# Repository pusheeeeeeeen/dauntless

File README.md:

# LiHv battery charger V1+V2
LiHv battery charger capable of charging LiHv batteries up to 4.35v, custom 3d designed case for 3d printing and an on-off switch. V1 is the simplest module, just to be available for cheaper and easier production of 4.35v LiHv chargers. V2 is equipped with a buzzer, OLED display, and XIAO RP2040 module to track battery percentage, and to alert the user when the battery is done charging. 

## V1: Mr. Barebones
### 3D rendering

### Schematic

### PCB Layout

## V2: The Upgrade
### 3D rendering

### Schematic

### PCB Layout

## BOM:
https://docs.google.com/spreadsheets/d/1y4eYakeZhQ_Du6QSC2gYvQQuMS255J4ouP4txh3QHf0/edit?gid=0#gid=0

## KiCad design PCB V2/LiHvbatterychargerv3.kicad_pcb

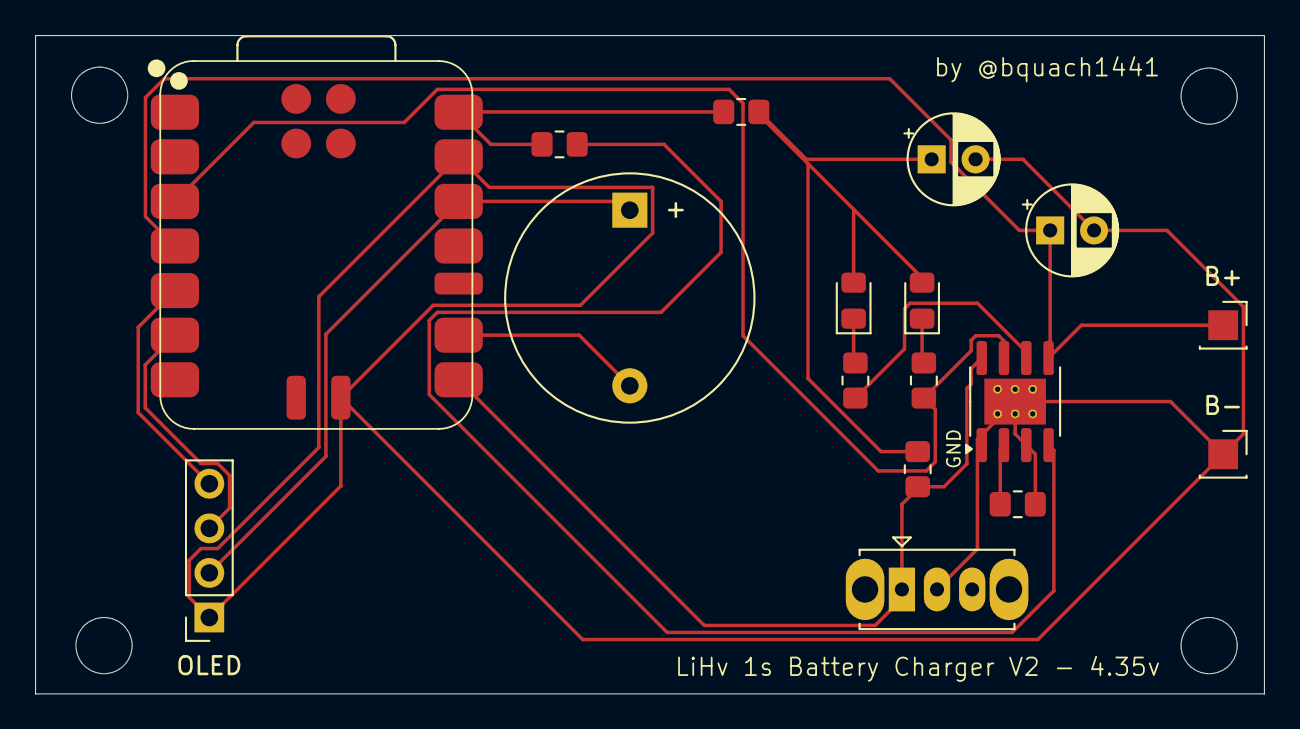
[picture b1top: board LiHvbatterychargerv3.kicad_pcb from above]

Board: 2 copper layers, 70.0 x 37.5 mm, 17 parts (0 on the bottom side), 15 nets.

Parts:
B+: Conn_01x01; PinSocket_1x01_P2.54mm_Vertical
B-: Conn_01x01; PinSocket_1x01_P2.54mm_Vertical
BZ1: Buzzer; Buzzer_D14mm_H7mm_P10mm
C2, C3: 10uF; CP_Radial_D5.0mm_P2.50mm
D1, D2: LED; LED_0805_2012Metric_Pad1.15x1.40mm_HandSolder
OLED: "OLED Display"; PinSocket_1x04_P2.54mm_Vertical
R3: 2.2k; R_0805_2012Metric_Pad1.20x1.40mm_HandSolder
R4, R5: 1k; R_0805_2012Metric_Pad1.20x1.40mm_HandSolder
R6, R8: 0.2; R_0805_2012Metric_Pad1.20x1.40mm_HandSolder
R7: 10k; R_0805_2012Metric_Pad1.20x1.40mm_HandSolder
SW1: SW_SPST; SW_Slide_SPDT_Straight_CK_OS102011MS2Q
U1: TP4056X-42-ESOP8; SOIC-8-1EP_3.9x4.9mm_P1.27mm_EP2.62x3.51mm_ThermalVias
U2: XIAO-RP2040-SMD

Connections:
GND: B-.1, C2.2, C3.2, OLED.1, R3.1, SW1.2 (B), U1.1 (TEMP), U1.3 (GND), U1.9 (EPAD), U2.13 (GND), U2.33 (GND)
unnamed: BZ1.1 (+), OLED.2, U2.12 (3V3)
unnamed: BZ1.2 (-), U2.9 (P2_D8_SCK)
unnamed: C2.1, D1.2 (A), D2.2 (A), R6.1, R7.2
unnamed: D1.1 (K), R5.2
unnamed: D2.1 (K), R4.2
unnamed: OLED.3, U2.6 (P7_SCL_D5)
unnamed: OLED.4, U2.5 (P6_SDA_D4)
unnamed: B+.1, C3.1, U1.5 (BAT), U2.4 (P29_A3_D3)
unnamed: R7.1, SW1.1 (A), U1.8 (CE), U2.8 (P1_D7_RX)
unnamed: R3.2, U1.2 (PROG)
unnamed: R8.1, U1.4 (V_{CC})
unnamed: R5.1, U1.7 (~CHRG), U2.3 (P28_A2_D2)
unnamed: R4.1, U1.6 (~STDBY)
unnamed: R6.2, R8.2, U2.14 (VBUS)

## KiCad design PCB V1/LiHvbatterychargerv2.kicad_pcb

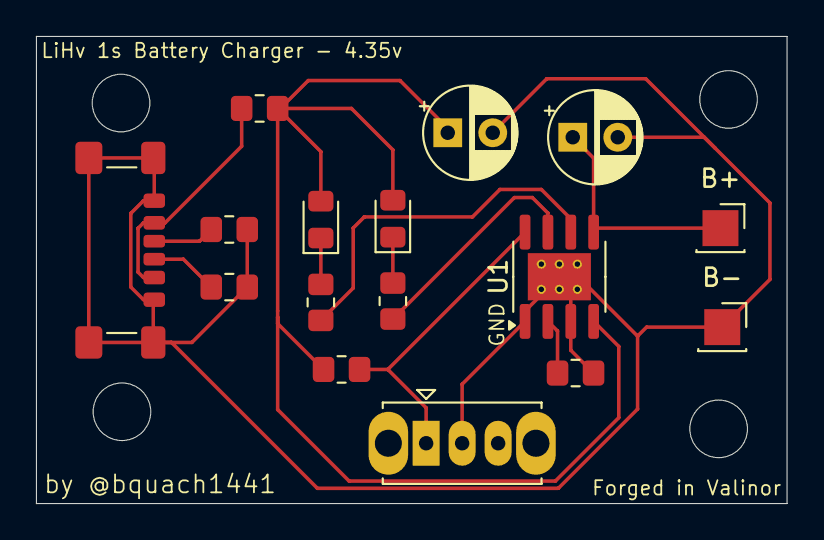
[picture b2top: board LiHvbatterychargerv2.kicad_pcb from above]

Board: 2 copper layers, 41.7 x 25.9 mm, 16 parts (0 on the bottom side), 12 nets.

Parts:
B+: Conn_01x01; PinSocket_1x01_P2.54mm_Vertical
B-: Conn_01x01; PinSocket_1x01_P2.54mm_Vertical
C2, C3: 10uF; CP_Radial_D5.0mm_P2.50mm
D1, D2: LED; LED_0805_2012Metric_Pad1.15x1.40mm_HandSolder
J1: USB_C_Receptacle_PowerOnly_6P; USB_C_Receptacle_GCT_USB4135-GF-A_6P_TopMnt_Horizontal
R1, R2: 5.1k; R_0805_2012Metric_Pad1.20x1.40mm_HandSolder
R3: 2.2k; R_0805_2012Metric_Pad1.20x1.40mm_HandSolder
R4, R5: 1k; R_0805_2012Metric_Pad1.20x1.40mm_HandSolder
R6: 0.2; R_0805_2012Metric_Pad1.20x1.40mm_HandSolder
R7: 10k; R_0805_2012Metric_Pad1.20x1.40mm_HandSolder
SW1: SW_SPST; SW_Slide_SPDT_Straight_CK_OS102011MS2Q
U1: TP4056X-42-ESOP8; SOIC-8-1EP_3.9x4.9mm_P1.27mm_EP2.62x3.51mm_ThermalVias

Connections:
GND: B-.1, C2.2, C3.2, J1.A12 (GND), J1.B12 (GND), J1.S1 (SHIELD), R1.2, R2.2, R3.1, SW1.2 (B), U1.1 (TEMP), U1.3 (GND), U1.9 (EPAD)
unnamed: C2.1, D1.2 (A), D2.2 (A), R6.1, R7.2, U1.4 (V_{CC})
unnamed: D1.1 (K), R5.2
unnamed: D2.1 (K), R4.2
unnamed: J1.A5 (CC1), R1.1
unnamed: J1.B5 (CC2), R2.1
unnamed: J1.A9 (VBUS), J1.B9 (VBUS), R6.2
unnamed: B+.1, C3.1, U1.5 (BAT)
unnamed: R7.1, SW1.1 (A), U1.8 (CE)
unnamed: R3.2, U1.2 (PROG)
unnamed: R5.1, U1.7 (~CHRG)
unnamed: R4.1, U1.6 (~STDBY)

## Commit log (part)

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2026-06-17 Create LICENSE
2026-06-20 Create placeholder
2026-06-20 Added PCBV1 files
2026-06-20 Create PCB V2
2026-06-20 Added PCB V2 files
2026-06-20 Added enclosure 3mf files for V1
2026-06-20 Rename LiHvbatterychargerv3.csv to bomV2.csv
